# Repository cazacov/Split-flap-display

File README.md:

# Split-flap Displays

## Omega

See [Omega_Controller_Hardware](./Omega_Controller_Hardware/) folder

## AEG

## Other Web Resources 

https://github.com/c3dprk/split-flap

https://fallblatt.blogspot.com/

https://github.com/adfinis-sygroup/sbb-fallblatt

https://www.thingiverse.com/thing:2369832

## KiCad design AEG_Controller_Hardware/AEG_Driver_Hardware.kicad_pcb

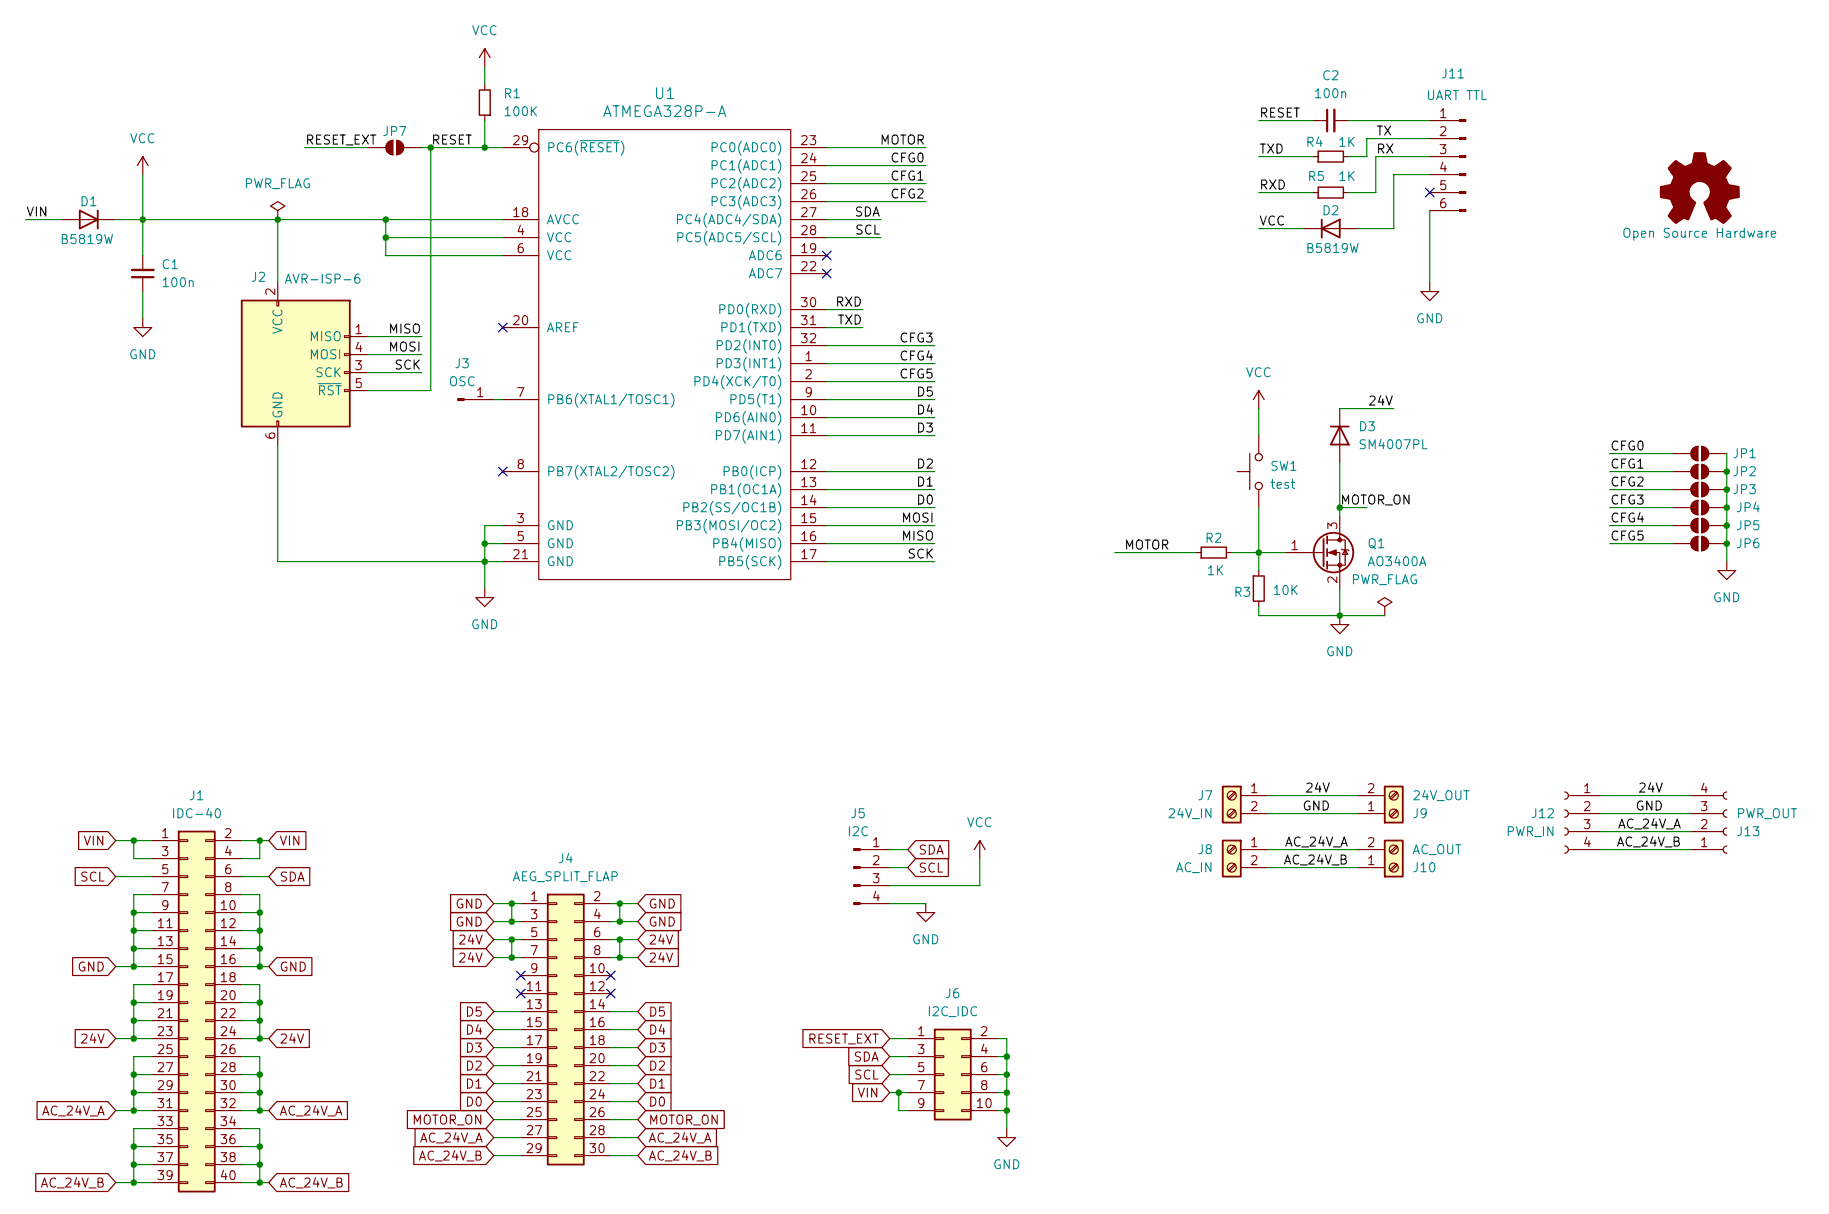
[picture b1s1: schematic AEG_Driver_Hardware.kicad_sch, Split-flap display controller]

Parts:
C1, C2: 100n; C_1206_3216Metric; LCSC C24497
D1, D2: B5819W; D_SOD-123; LCSC C8598
D3: SM4007PL; D_SOD-123F; LCSC C64898
J1: IDC-40; IDC-Header_2x20_P2.54mm_Vertical
J2: AVR-ISP-6; IDC-Header_2x03_P2.54mm_Vertical
J3: OSC; PinHeader_1x01_P2.54mm_Vertical
J4: AEG_SPLIT_FLAP; AEG_Split_Flap_15_PTH
J5: I2C; PinHeader_1x04_P2.54mm_Vertical
J6: I2C_IDC; IDC-Header_2x05_P2.54mm_Vertical
J7: 24V_IN; TerminalBlock_bornier-2_P5.08mm
J8: AC_IN; TerminalBlock_bornier-2_P5.08mm
J9: 24V_OUT; TerminalBlock_bornier-2_P5.08mm
J10: AC_OUT; TerminalBlock_bornier-2_P5.08mm
J11: UART TTL; PinHeader_1x06_P2.54mm_Vertical
J12: PWR_IN; PinHeader_1x04_P2.54mm_Vertical
J13: PWR_OUT; PinHeader_1x04_P2.54mm_Vertical
JP1, JP2, JP3, JP4, JP5, JP6, JP7: SolderJumper_2_Open; SolderJumper-2_P1.3mm_Open_RoundedPad1.0x1.5mm
Q1: AO3400A; SOT-23; LCSC C20917
R1: 100K; R_1206_3216Metric_Pad1.30x1.75mm_HandSolder; LCSC C17900
R2, R4, R5: 1K; R_1206_3216Metric_Pad1.30x1.75mm_HandSolder; LCSC C4410
R3: 10K; R_1206_3216Metric_Pad1.30x1.75mm_HandSolder; LCSC C17902
SW1: test; SW_PUSH_6mm_H4.3mm
U1: ATMEGA328P-A; TQFP-32_7x7mm_P0.8mm; LCSC C14877

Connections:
24V: D3.1 (K), J1.17, J1.18, J1.19, J1.20, J1.21, J1.22, J1.23, J1.24, J4.5, J4.6, J4.7, J4.8, J7.1, J9.2, J12.1, J13.4
/CFG0: JP1.1 (A), U1.24 (PC1(ADC1))
/CFG1: JP2.1 (A), U1.25 (PC2(ADC2))
/CFG2: JP3.1 (A), U1.26 (PC3(ADC3))
/CFG3: JP4.1 (A), U1.32 (PD2(INT0))
/CFG4: JP5.1 (A), U1.1 (PD3(INT1))
/CFG5: JP6.1 (A), U1.2 (PD4(XCK/T0))
/MISO: J2.1 (MISO), U1.16 (PB4(MISO))
/MOSI: J2.4 (MOSI), U1.15 (PB3(MOSI/OC2))
/MOTOR: R2.1, U1.23 (PC0(ADC0))
/RESET: C2.1, J2.5 (~RST), JP7.2 (B), R1.1, U1.29 (PC6(~RESET))
/RX: J11.3, R5.2
/RXD: R5.1, U1.30 (PD0(RXD))
/SCK: J2.3 (SCK), U1.17 (PB5(SCK))
/TX: J11.2, R4.2
/TXD: R4.1, U1.31 (PD1(TXD))
AC_24V_A: J1.25, J1.26, J1.27, J1.28, J1.29, J1.30, J1.31, J1.32, J4.27, J4.28, J8.1, J10.2, J12.3, J13.2
AC_24V_B: J1.33, J1.34, J1.35, J1.36, J1.37, J1.38, J1.39, J1.40, J4.29, J4.30, J8.2, J10.1, J12.4, J13.1
D0: J4.23, J4.24, U1.14 (PB2(SS/OC1B))
D1: J4.21, J4.22, U1.13 (PB1(OC1A))
D2: J4.19, J4.20, U1.12 (PB0(ICP))
D3: J4.17, J4.18, U1.11 (PD7(AIN1))
D4: J4.15, J4.16, U1.10 (PD6(AIN0))
D5: J4.13, J4.14, U1.9 (PD5(T1))
GND: C1.1, J1.7, J1.8, J1.9, J1.10, J1.11, J1.12, J1.13, J1.14, J1.15, J1.16, J2.6 (GND), J4.1, J4.2, J4.3, J4.4, J5.4, J6.2, J6.4, J6.6, J6.8, J6.10, J7.2, J9.1, J11.6, J12.2, J13.3, JP1.2 (B), JP2.2 (B), JP3.2 (B), JP4.2 (B), JP5.2 (B), JP6.2 (B), Q1.2 (S), R3.2, U1.3 (GND), U1.5 (GND), U1.21 (GND)
MOTOR_ON: D3.2 (A), J4.25, J4.26, Q1.3 (D)
unnamed: D2.2 (A), J11.4
unnamed: J3.1, U1.7 (PB6(XTAL1/TOSC1))
unnamed: C2.2, J11.1
unnamed: Q1.1 (G), R2.2, R3.1, SW1.1
RESET_EXT: J6.1, JP7.1 (A)
SCL: J1.5, J5.2, J6.5, U1.28 (PC5(ADC5/SCL))
SDA: J1.6, J5.1, J6.3, U1.27 (PC4(ADC4/SDA))
VCC: C1.2, D1.1 (K), D2.1 (K), J2.2 (VCC), J5.3, R1.2, SW1.2, U1.4 (VCC), U1.6 (VCC), U1.18 (AVCC)
VIN: D1.2 (A), J1.1, J1.2, J1.3, J1.4, J6.7, J6.9

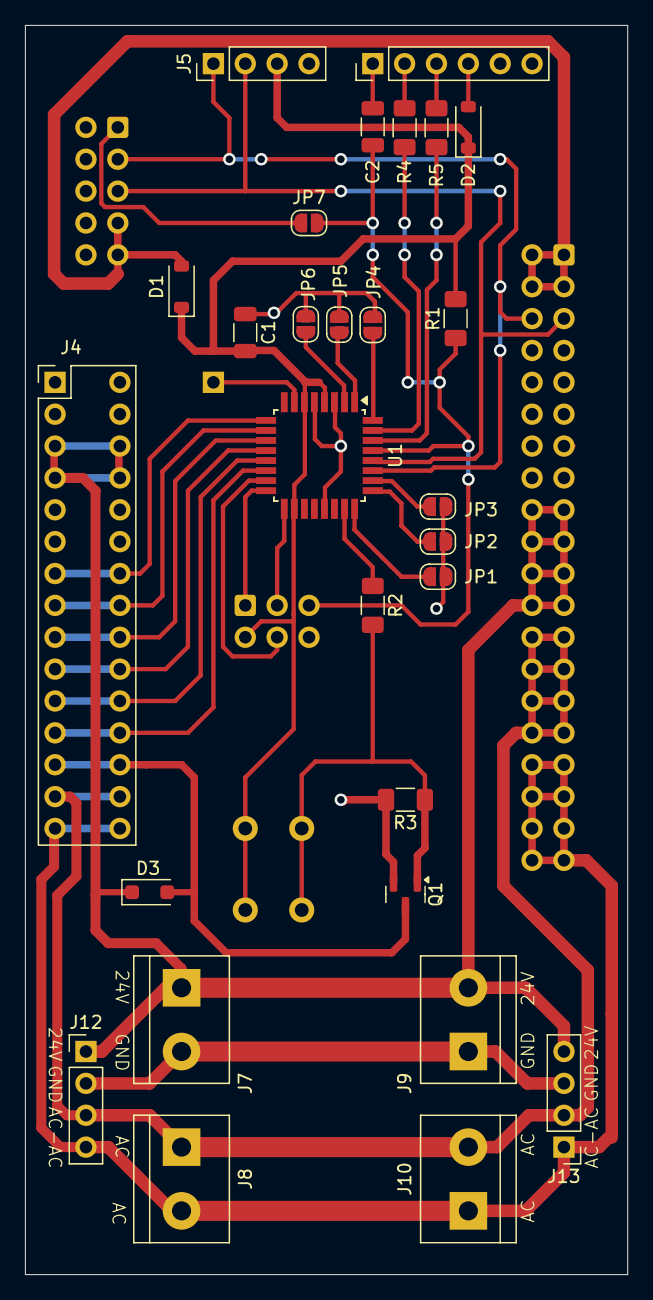
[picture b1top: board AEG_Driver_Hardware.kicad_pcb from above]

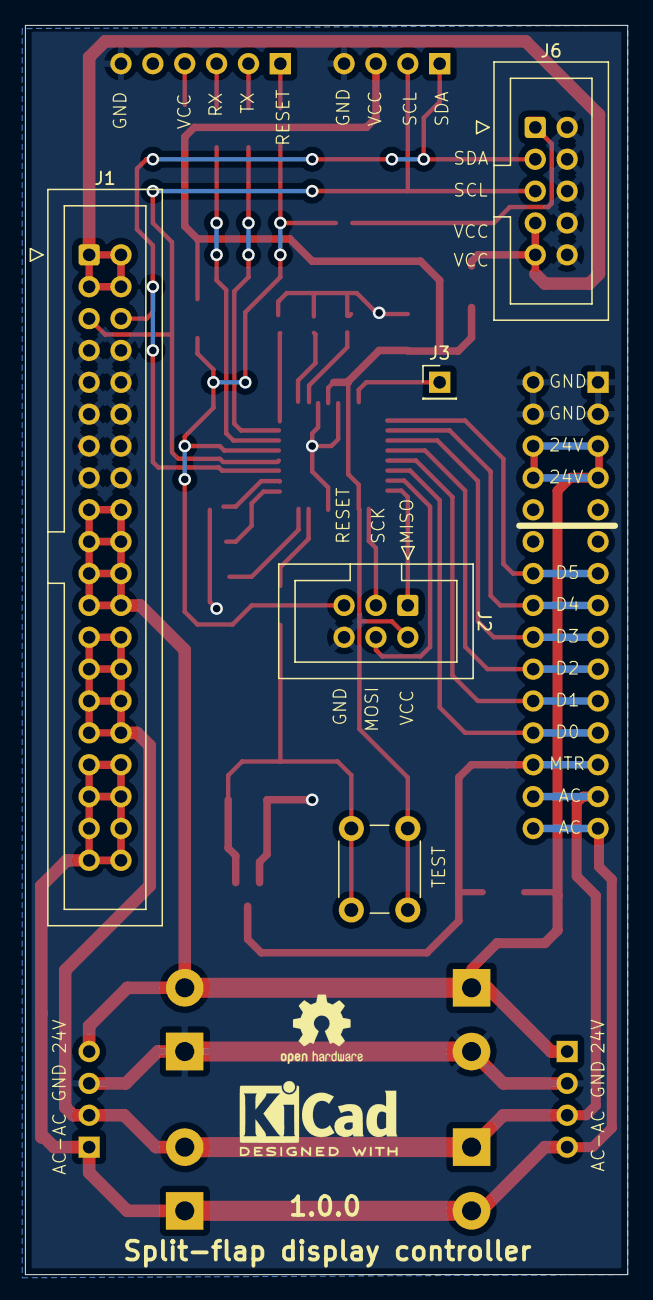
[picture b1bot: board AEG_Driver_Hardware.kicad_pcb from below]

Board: 2 copper layers, 48.0 x 99.6 mm, 33 parts (5 on the bottom side), 35 nets.

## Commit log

2025-09-14 Omega model
2025-09-15 AEG KiCad project, version 1.0.0
2025-09-15 README
